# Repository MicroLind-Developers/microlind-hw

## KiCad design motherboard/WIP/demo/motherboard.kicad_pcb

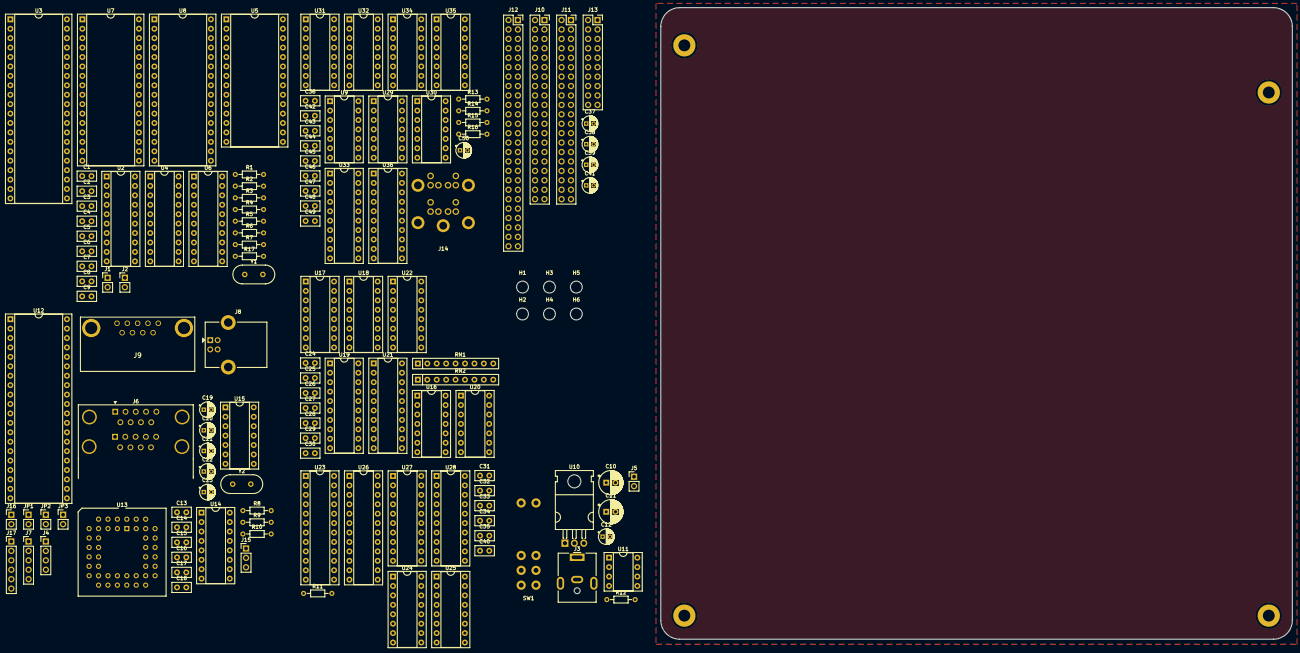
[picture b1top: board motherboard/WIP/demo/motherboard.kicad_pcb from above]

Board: 4 copper layers, 170.2 x 170.2 mm, 134 parts (0 on the bottom side), 218 nets, no tracks yet.

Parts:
C1, C2: 22pF; C_Disc_D5.0mm_W2.5mm_P2.50mm
C3, C4, C5, C6, C7, C8, C9, C13, C14, C17, C18, C24, C25, C26, C27, C28, C29, C30, C31, C32, C33, C34, C35, C36, C40, C42, C43, C44, C45, C46, C47, C48, C49: 100n; C_Disc_D5.0mm_W2.5mm_P2.50mm
C10: 33µF; CP_Radial_D6.3mm_P2.50mm
C11: 100µF; CP_Radial_D6.3mm_P2.50mm
C12: 10µF; CP_Radial_D4.0mm_P2.00mm
C15, C16: 43pF; C_Disc_D5.0mm_W2.5mm_P2.50mm
C19, C20, C21, C22, C23: 1u; CP_Radial_D4.0mm_P2.00mm
C37, C38, C39, C41, C50: 10u; CP_Radial_D4.0mm_P2.00mm
H1, H2, H3, H4, H5, H6: MountingHole; MountingHole_3.2mm_M3_ISO7380
J1: HALT; PinHeader_1x02_P2.54mm_Vertical
J2: Write Enable; PinHeader_1x02_P2.54mm_Vertical
J3: Power; BarrelJack_CUI_PJ-063AH_Horizontal
J4: PowerLed; PinHeader_1x04_P2.54mm_Vertical
J5: Reset; PinHeader_1x02_P2.54mm_Vertical
J6: Joystic Ports; DSUB-9-Double_NorComp
J7: POT Con; PinHeader_1x05_P2.54mm_Vertical
J8: Console; USB_B_Lumberg_2411_02_Horizontal
J9: Serial; 23018431
J10: VideoAddon; PinSocket_2x20_P2.54mm_Vertical
J11: AudioAddon; PinSocket_2x20_P2.54mm_Vertical
J12: ExpansionPort; PinSocket_2x25_P2.54mm_Vertical
J13: Compact Flash Addon; PinSocket_2x10_P2.54mm_Vertical
J14: 2xPS2-Mini-Din
J15: PC Speaker; PinHeader_1x03_P2.54mm_Vertical
J16: LPen; PinHeader_1x02_P2.54mm_Vertical
J17: Clock Exp.; PinHeader_1x06_P2.54mm_Vertical
JP1: Reset EN; PinHeader_1x02_P2.54mm_Vertical
JP2: RTS; PinHeader_1x02_P2.54mm_Vertical
JP3: CTS; PinHeader_1x02_P2.54mm_Vertical
R1, R2, R3, R4, R5, R6, R7, R11, R12, R17: 4k7; R_Axial_DIN0204_L3.6mm_D1.6mm_P7.62mm_Horizontal
R8, R9, R10: 1k; R_Axial_DIN0204_L3.6mm_D1.6mm_P7.62mm_Horizontal
R13, R14, R15, R16: 10k; R_Axial_DIN0204_L3.6mm_D1.6mm_P7.62mm_Horizontal
RN1, RN2: R_Network08; R_Array_SIP9
SW1: Power Switch; CMD-Switch
U1: mITX
U2, U4, U6, U28: 74HC245; DIP-20_W7.62mm_Socket
U3: MC6809; DIP-40_W15.24mm_Socket
U5: 28C64; DIP-28_W15.24mm_Socket
U7, U8: AS6C4008; DIP-32_W15.24mm_Socket
U9, U30: 74HCT14; DIP-14_W7.62mm_Socket
U10: BA05CCOT; TO-220-3_Horizontal_TabDown
U11: MAX708; DIP-8_W7.62mm_Socket
U12: 65c22; DIP-40_W15.24mm_Socket
U13: XR88C92; PLCC-44_THT-Socket
U14: MAX232; DIP-16_W7.62mm_Socket
U15: MCP2221A; DIP-14_W7.62mm_Socket
U16: 74HCT02; DIP-14_W7.62mm_Socket
U17, U18: 74HCT148; DIP-16_W7.62mm_Socket
U19, U21: 74HCT574; DIP-20_W7.62mm_Socket
U20: 74HCT00; DIP-14_W7.62mm_Socket
U22: 74HCT85; DIP-16_W7.62mm_Socket
U23, U26: GAL 22V10; DIP-24_W7.62mm_Socket
U24, U25: 74LS670; DIP-16_W7.62mm_Socket
U27: GAL16V8; DIP-20_W7.62mm_Socket
U29: 74HCT32; DIP-14_W7.62mm_Socket
U31, U32, U34, U35: 74HCT595; DIP-16_W7.62mm_Socket
U33, U36: 74HCT573; DIP-20_W7.62mm_Socket
Y1: 12MHz; Crystal_HC49-U_Vertical
Y2: 3.3864; Crystal_HC49-U_Vertical

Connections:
/A0: J10.32, J11.32, J12.32, J13.6, U2.2 (A0), U5.10 (A0), U7.12 (A0), U8.12 (A0), U12.38 (RS0), U13.2 (A0), U23.10 (I10), U24.14 (Wa), U25.14 (Wa), U26.1 (I1/CLK), U29.4, U30.3
/A1: J10.30, J11.30, J12.30, J13.8, U2.3 (A1), U5.9 (A1), U7.11 (A1), U8.11 (A1), U12.37 (RS1), U13.4 (A1), U23.11 (I11), U24.13 (Wb), U25.13 (Wb), U26.2 (I2)
/A2: J10.28, J11.28, J12.28, J13.10, U2.4 (A2), U5.8 (A2), U7.10 (A2), U8.10 (A2), U12.36 (RS2), U13.6 (A2), U26.3 (I3)
/A3: J10.26, J11.26, J12.26, U2.5 (A3), U5.7 (A3), U7.9 (A3), U8.9 (A3), U12.35 (RS3), U13.7 (A3), U26.4 (I4)
/A4: J10.24, J11.24, J12.24, U2.6 (A4), U5.6 (A4), U7.8 (A4), U8.8 (A4), U26.5 (I5)
/A5: J10.22, J11.22, J12.22, U2.7 (A5), U5.5 (A5), U7.7 (A5), U8.7 (A5), U26.6 (I6)
/A6: J10.20, J11.20, J12.20, U2.8 (A6), U5.4 (A6), U7.6 (A6), U8.6 (A6), U26.7 (I7)
/A7: J10.18, J11.18, J12.18, U2.9 (A7), U5.3 (A7), U7.5 (A7), U8.5 (A7), U26.8 (I8)
/A8: J10.19, J11.19, J12.19, U4.2 (A0), U5.25 (A8), U7.27 (A8), U8.27 (A8), U26.9 (I9)
/A9: J10.21, J11.21, J12.21, U4.3 (A1), U5.24 (A9), U7.26 (A9), U8.26 (A9), U26.10 (I10)
/A10: J10.27, J11.27, J12.27, U4.4 (A2), U5.21 (A10), U7.23 (A10), U8.23 (A10), U23.1 (I1/CLK)
/A11: J10.23, J11.23, J12.23, U4.5 (A3), U5.23 (A11), U7.25 (A11), U8.25 (A11), U23.2 (I2)
/A12: J10.16, J11.16, J12.16, U4.6 (A4), U5.2 (A12), U7.4 (A12), U8.4 (A12), U23.3 (I3)
/A13: J10.17, J11.17, J12.17, U4.7 (A5), U7.28 (A13), U8.28 (A13), U23.4 (I4)
/A14: J12.42, U4.8 (A6), U23.5 (I5)
/A15: J12.44, U4.9 (A7), U23.6 (I6)
/AM14: J10.14, J12.14, U7.3 (A14), U8.3 (A14), U24.10 (Q1), U28.18 (B0)
/AM15: J10.11, J12.11, U7.31 (A15), U8.31 (A15), U24.9 (Q2), U28.17 (B1)
/AM16: J10.12, J12.12, U7.2 (A16), U8.2 (A16), U24.7 (Q3), U28.16 (B2)
/AM17: J10.13, J12.13, U7.30 (A17), U8.30 (A17), U24.6 (Q4), U28.15 (B3)
/AM18: J10.10, J12.10, U7.1 (A18), U8.1 (A18), U25.10 (Q1), U28.14 (B4)
/AM19: J10.9, J12.9, U23.7 (I7), U25.9 (Q2), U28.13 (B5)
/AM20: J10.8, J12.8, U23.8 (I8), U25.7 (Q3), U28.12 (B6)
/AM21: J12.46, U23.9 (I9), U25.6 (Q4), U28.11 (B7)
/Address-Logic/A14/A0: U23.17 (IO7), U24.5 (Ra), U25.5 (Ra)
/Address-Logic/A15/A1: U23.16 (IO8), U24.4 (Rb), U25.4 (Rb)
/Address-Logic/BA: U2.19 (CE), U3.6 (BA), U4.19 (CE), U6.19 (CE), U27.4 (I4)
/Address-Logic/BS: U3.5 (BS), U27.5 (I5)
/Address-Logic/Q: U3.35 (Q), U21.11 (Cp), U27.2 (I2)
/Address-Logic/~CF_EN: J13.7, U26.17 (IO7)
/Address-Logic/~EXP_EN: J12.43, U26.14 (I010)
/Address-Logic/~IO_EN: U23.19 (IO5), U26.11 (I11)
/Address-Logic/~IRQ_EN: U16.3, U16.5, U26.22 (IO2)
/Address-Logic/~MAP_RD: U23.18 (IO6), U24.11 (~Er), U25.11 (~Er)
/Address-Logic/~MEM_EN: U26.23 (IO1), U27.6 (I6)
/Address-Logic/~MEM_RD: U23.13 (I12), U27.16 (IO4), U28.19 (CE)
/Address-Logic/~MEM_WR: U24.12 (~Ew), U25.12 (~Ew), U27.15 (IO5)
/Address-Logic/~PAR_EN: U12.23 (~CS2), U26.19 (IO5)
/Address-Logic/~PS2_EN: U26.18 (IO6), U29.2
/Address-Logic/~RAMH_EN: U8.22 (CE#), U23.21 (I03)
/Address-Logic/~RAML_EN: U7.22 (CE#), U23.22 (IO2)
/Address-Logic/~ROM_EN: U5.20 (~CE), U23.23 (IO1)
/Address-Logic/~SER_EN: U13.39 (~CS), U26.20 (IO4)
/Address-Logic/~SND_EN: J11.3, U26.16 (IO8)
/Address-Logic/~VDC_EN: J10.29, U26.15 (IO9)
/CPU_MEM/MRDY: R6.1, U3.36 (MRDY)
/CPU_MEM/pA0: U2.18 (B0), U3.8 (A0)
/CPU_MEM/pA1: U2.17 (B1), U3.9 (A1)
/CPU_MEM/pA2: U2.16 (B2), U3.10 (A2)
/CPU_MEM/pA3: U2.15 (B3), U3.11 (A3)
/CPU_MEM/pA4: U2.14 (B4), U3.12 (A4)
/CPU_MEM/pA5: U2.13 (B5), U3.13 (A5)
/CPU_MEM/pA6: U2.12 (B6), U3.14 (A6)
/CPU_MEM/pA7: U2.11 (B7), U3.15 (A7)
/CPU_MEM/pA8: U3.16 (A8), U4.18 (B0)
/CPU_MEM/pA9: U3.17 (A9), U4.17 (B1)
/CPU_MEM/pA10: U3.18 (A10), U4.16 (B2)
/CPU_MEM/pA11: U3.19 (A11), U4.15 (B3)
/CPU_MEM/pA12: U3.20 (A12), U4.14 (B4)
/CPU_MEM/pA13: U3.21 (A13), U4.13 (B5)
/CPU_MEM/pA14: U3.22 (A14), U4.12 (B6)
/CPU_MEM/pA15: U3.23 (A15), U4.11 (B7)
/CPU_MEM/pD0: U3.31 (D0), U6.18 (B0)
/CPU_MEM/pD1: U3.30 (D1), U6.17 (B1)
/CPU_MEM/pD2: U3.29 (D2), U6.16 (B2)
/CPU_MEM/pD3: U3.28 (D3), U6.15 (B3)
/CPU_MEM/pD4: U3.27 (D4), U6.14 (B4)
/CPU_MEM/pD5: U3.26 (D5), U6.13 (B5)
/CPU_MEM/pD6: U3.25 (D6), U6.12 (B6)
/CPU_MEM/pD7: U3.24 (D7), U6.11 (B7)
/CPU_MEM/~FIRQ: R4.1, U3.4 (~FIRQ), U22.7 (Oa<b)
/CPU_MEM/~HALT: J1.2, R7.1, U3.40 (~HALT)
/CPU_MEM/~IRQ: R3.1, U3.3 (~IRQ), U12.21 (~IRQ)
/CPU_MEM/~NMI: R2.1, U3.2 (~NMI)
/D0: J10.34, J11.34, J12.34, J13.11, U5.11 (D0), U6.2 (A0), U7.13 (DQ0), U8.13 (DQ0), U12.33 (D0), U13.28 (D0), U21.19 (Q0), U24.15 (D1), U28.2 (A0), U33.19 (Q0), U36.19 (Q0)
/D1: J10.36, J11.36, J12.36, J13.12, U5.12 (D1), U6.3 (A1), U7.14 (DQ1), U8.14 (DQ1), U12.32 (D1), U13.18 (D1), U21.18 (Q1), U24.1 (D2), U28.3 (A1), U33.18 (Q1), U36.18 (Q1)
/D2: J10.38, J11.38, J12.38, J13.13, U5.13 (D2), U6.4 (A2), U7.15 (DQ2), U8.15 (DQ2), U12.31 (D2), U13.27 (D2), U21.17 (Q2), U24.2 (D3), U28.4 (A2), U33.17 (Q2), U36.17 (Q2)
/D3: J10.39, J11.39, J12.39, J13.14, U5.15 (D3), U6.5 (A3), U7.17 (DQ3), U8.17 (DQ3), U12.30 (D3), U13.19 (D3), U21.16 (Q3), U24.3 (D4), U28.5 (A3), U33.16 (Q3), U36.16 (Q3)
/D4: J10.37, J11.37, J12.37, J13.15, U5.16 (D4), U6.6 (A4), U7.18 (DQ4), U8.18 (DQ4), U12.29 (D4), U13.26 (D4), U19.2 (D0), U21.15 (Q4), U25.15 (D1), U28.6 (A4), U33.15 (Q4), U36.15 (Q4)
/D5: J10.35, J11.35, J12.35, J13.16, U5.17 (D5), U6.7 (A5), U7.19 (DQ5), U8.19 (DQ5), U12.28 (D5), U13.20 (D5), U19.3 (D1), U21.14 (Q5), U25.1 (D2), U28.7 (A5), U33.14 (Q5), U36.14 (Q5)
/D6: J10.33, J11.33, J12.33, J13.17, U5.18 (D6), U6.8 (A6), U7.20 (DQ6), U8.20 (DQ6), U12.27 (D6), U13.25 (D6), U19.4 (D2), U21.13 (Q6), U25.2 (D3), U28.8 (A6), U33.13 (Q6), U36.13 (Q6)
/D7: J10.31, J11.31, J12.31, J13.18, U5.19 (D7), U6.9 (A7), U7.21 (DQ7), U8.21 (DQ7), U12.26 (D7), U13.21 (D7), U19.5 (D3), U21.12 (Q7), U25.3 (D4), U28.9 (A7), U33.12 (Q7), U36.12 (Q7)
/Expansion Ports/BAVAIL: J10.7, J12.7, U27.17 (I03)
/Expansion Ports/E: J10.5, J11.5, J12.5, J13.3, U3.34 (E), U12.25 (ϕ2), U27.1 (I1/CLK), U31.12 (RCLK), U32.12 (RCLK), U34.12 (RCLK), U35.12 (RCLK)
/Expansion Ports/R/~W: J10.6, J11.6, J12.6, U3.32 (R/~W), U6.1 (A->B), U12.22 (R/~W), U27.3 (I3)
/Expansion Ports/~BREQ: J10.3, J12.3, R5.1, U3.33 (~DMA/BREQ), U27.11 (I10/~OE)
/Expansion Ports/~MAP_EN: J12.41, R11.1, U23.14 (I010)
/Expansion Ports/~RAMX_EN: J12.29, U23.20 (IO4)
/Expansion Ports/~RD: J10.25, J11.25, J12.25, J13.5, U5.22 (~OE), U7.24 (OE#), U8.24 (OE#), U13.10 (~RD), U16.2, U27.18 (IO2), U29.1
/Expansion Ports/~RST: J10.2, J11.2, J12.2, J13.2, JP1.2 (B), R1.1, U3.37 (~RESET), U11.7 (~RST), U12.34 (~RES), U31.10 (~SRCLR), U32.10 (~SRCLR), U34.10 (~SRCLR), U35.10 (~SRCLR)
/Expansion Ports/~WR: J2.2, J10.15, J11.15, J12.15, J13.4, U7.29 (WE#), U8.29 (WE#), U13.9 (~WR), U16.6, U26.13 (I12), U27.19 (IO1)
/PS2/M_CLK: U9.2, U31.11 (SRCLK), U32.11 (SRCLK)
/PS2/M_DATA: U9.4, U31.14 (SER)
/PS2/PS2_KB_CLK: J14.11 (Kbd_Clock), R15.2, U30.1
/PS2/PS2_KB_DATA: J14.7 (Kbd_Data), R16.2, U30.5
/PS2/PS2_M_CLK: J14.5 (Mouse_Clock), R13.2, U9.13
/PS2/PS2_M_DATA: J14.1 (Mouse_Data), R14.2, U9.11
/Power-Management/RST: U11.8 (RST), U13.38 (RST)
/Serial-Parallel/D+: J8.3 (D+), U15.13 (D+)
/Serial-Parallel/D-: J8.2 (D-), U15.12 (D-)
/~IRQ_0: RN2.6 (R5), U13.24 (~INT), U18.4 (I7)
/~IRQ_1: RN2.7 (R6), U18.3 (I6)
/~IRQ_2: J10.4, RN2.8 (R7), U18.2 (I5)
/~IRQ_3: RN2.9 (R8), U18.1 (I4)
/~IRQ_4: RN2.5 (R4), U18.13 (I3)
/~IRQ_5: RN2.4 (R3), U18.12 (I2)
/~IRQ_6: RN2.3 (R2), U18.11 (I1)
/~IRQ_7: J11.4, RN2.2 (R1), U18.10 (IO)
/~IRQ_8: J12.4, RN1.6 (R5), U17.4 (I7)
/~IRQ_9: RN1.7 (R6), U17.3 (I6)
/~IRQ_10: RN1.8 (R7), U17.2 (I5)
/~IRQ_11: RN1.9 (R8), U17.1 (I4)
/~IRQ_12: RN1.5 (R4), U17.13 (I3)
/~IRQ_13: RN1.4 (R3), U17.12 (I2)
/~IRQ_14: RN1.3 (R2), U17.11 (I1)
GND: C1.2, C2.2, C3.2, C4.2, C5.2, C6.2, C7.2, C8.2, C9.2, C10.2, C11.2, C12.2, C13.2, C14.2, C15.2, C16.2, C17.2, C18.2, C22.2, C23.2, C24.2, C25.2, C26.2, C27.2, C28.2, C29.2, C30.2, C31.2, C32.2, C33.2, C34.2, C35.2, C36.2, C37.2, C38.2, C39.2, C40.2, C41.2, C42.2, C43.2, C44.2, C45.2, C46.2, C47.2, C48.2, C49.2, C50.2, J1.1, J3.2, J3.MP (MountPin), J4.1 (K), J5.1, J6.8, J6.18, J7.3, J8.4 (GND), J8.5 (Shield), J9.5, J10.40, J11.40, J12.40, J12.48, J12.50, J13.20, J14.3 (Mouse_GND), J14.9 (Kbd_GND), J14.G (GND), J15.1, J16.1, J17.1, R11.2, SW1.G (GND), U2.1 (A->B), U2.10 (GND), U3.1 (VSS), U4.1 (A->B), U4.10 (GND), U5.14 (GND), U6.10 (GND), U7.16 (VSS), U8.16 (VSS), U9.7 (GND), U10.2 (GND), U11.3 (GND), U12.1 (VSS), U13.22 (GND), U14.15 (GND), U15.14 (VSS), U16.7 (GND), U17.8 (GND), U18.5 (EI), U18.8 (GND), U19.1 (OE), U19.10 (GND), U20.7 (GND), U21.10 (GND), U22.2 (Ia<b), U22.3 (Ia=b), U22.4 (Ia>b), U22.8 (GND), U23.12 (GND), U24.8 (GND), U25.8 (GND), U26.12 (GND), U27.10 (GND), U28.1 (A->B), U28.10 (GND), U29.7 (GND), U29.12, U29.13, U30.7 (GND), U31.8 (GND), U31.13 (~OE), U32.8 (GND), U32.13 (~OE), U33.10 (GND), U34.8 (GND), U34.13 (~OE), U35.8 (GND), U35.13 (~OE), U36.10 (GND)
unnamed: J2.1, R17.1, U5.27 (~WE)
unnamed: J4.4 (BA), R10.1
unnamed: J4.3 (GA), R9.1
unnamed: J4.2 (RA), R8.1
unnamed: J6.5, J7.1
unnamed: J6.9, J7.2
unnamed: J6.15, J7.4
unnamed: J6.19, J7.5
unnamed: J15.2, U12.17 (PB7)
unnamed: J6.6, J16.2, U12.6 (PA4)
unnamed: J17.2, U12.18 (CB1)
unnamed: J17.3, U12.19 (CB2)
unnamed: J17.4, U12.40 (CA1)
unnamed: J17.5, U12.9 (PA7)
unnamed: JP1.1 (A), U15.4 (~RST)
unnamed: JP2.1 (A), U13.32 (OP0)
unnamed: JP2.2 (B), U15.2 (GP0)
unnamed: JP3.1 (A), U13.8 (IP0)
unnamed: JP3.2 (B), U15.3 (GP1)
unnamed: C10.1, SW1.3 (1-2), SW1.6 (2-2), U10.1 (Vin)
unnamed: J3.1, SW1.1 (1-C), SW1.4 (2-C)
unnamed: C2.1, U3.38 (EXTAL), Y1.1
unnamed: C1.1, U3.39 (XTAL), Y1.2
unnamed: U9.1, U9.12
unnamed: U9.3, U9.10
unnamed: J5.2, R12.2, U11.1 (~MR)
unnamed: J6.1, U12.2 (PA0)
unnamed: J6.2, U12.3 (PA1)
unnamed: J6.3, U12.4 (PA2)
unnamed: J6.4, U12.5 (PA3)
unnamed: J6.11, U12.10 (PB0)
unnamed: J6.12, U12.11 (PB1)
unnamed: J6.13, U12.12 (PB2)
unnamed: J6.14, U12.13 (PB3)
unnamed: J6.16, U12.14 (PB4)
unnamed: R8.2, U13.30 (OP4)
unnamed: R10.2, U13.16 (OP5)
unnamed: R9.2, U13.29 (OP6)
unnamed: U13.35 (RxA), U15.6 (UTx)
unnamed: U13.11 (RxB), U14.12 (R1OUT)
unnamed: U13.33 (TxA), U15.5 (URx)
unnamed: U13.13 (TxB), U14.11 (T1IN)
unnamed: C15.1, U13.36 (X1/CLK), Y2.2
unnamed: C16.1, U13.37 (X2), Y2.1
unnamed: C19.1, U14.1 (C1+)
unnamed: C19.2, U14.3 (C1-)
unnamed: C20.1, U14.4 (C2+)
unnamed: C20.2, U14.5 (C2-)
unnamed: J9.2, U14.13 (R1IN)
unnamed: J9.3, U14.14 (T1OUT)
unnamed: C21.1, U14.2 (VS+)
unnamed: C21.2, U14.6 (VS-)
unnamed: C23.1, U15.11 (VUSB)
unnamed: U16.1, U16.8, U16.9
unnamed: U17.5 (EI), U18.15 (EO)
unnamed: U17.9 (S0), U20.12
unnamed: U17.7 (S1), U20.9
unnamed: U17.6 (S2), U20.4
unnamed: U18.14 (GS), U20.1, U20.2
unnamed: U18.9 (S0), U20.13
unnamed: U18.7 (S1), U20.10
unnamed: U18.6 (S2), U20.5
unnamed: U16.4, U19.11 (Cp)
unnamed: U19.19 (Q0), U21.6 (D4), U22.10 (A0)
unnamed: U19.18 (Q1), U21.7 (D5), U22.12 (A1)
unnamed: U19.17 (Q2), U21.8 (D6), U22.13 (A2)
unnamed: U19.16 (Q3), U21.9 (D7), U22.15 (A3)
unnamed: U20.6, U21.2 (D0), U22.9 (B0)
unnamed: U20.8, U21.3 (D1), U22.11 (B1)
unnamed: U20.11, U21.4 (D2), U22.14 (B2)
unnamed: U20.3, U21.5 (D3), U22.1 (B3)
unnamed: U16.10, U21.1 (OE)
unnamed: U29.3, U29.5, U29.9
unnamed: U29.10, U30.4
unnamed: U30.6, U30.11
unnamed: U30.2, U30.13
unnamed: U31.2 (QC), U33.9 (D7)
unnamed: U31.3 (QD), U33.8 (D6)
unnamed: U31.4 (QE), U33.7 (D5)
unnamed: U31.5 (QF), U33.6 (D4)
unnamed: U31.6 (QG), U33.5 (D3)
unnamed: U31.9 (QH'), U32.14 (SER)
unnamed: U31.7 (QH), U33.4 (D2)
unnamed: U32.15 (QA), U33.3 (D1)
unnamed: U32.1 (QB), U33.2 (D0)
unnamed: U9.9, U32.2 (QC), U33.11 (Load)
unnamed: U29.8, U33.1 (OE)
unnamed: U34.2 (QC), U36.9 (D7)
unnamed: U34.3 (QD), U36.8 (D6)
unnamed: U34.4 (QE), U36.7 (D5)
unnamed: U34.5 (QF), U36.6 (D4)
unnamed: U34.6 (QG), U36.5 (D3)
unnamed: U34.9 (QH'), U35.14 (SER)
unnamed: U34.7 (QH), U36.4 (D2)
unnamed: U30.10, U34.14 (SER)
unnamed: U30.12, U34.11 (SRCLK), U35.11 (SRCLK)
unnamed: U35.15 (QA), U36.3 (D1)
unnamed: U35.1 (QB), U36.2 (D0)
unnamed: U30.9, U35.2 (QC), U36.11 (Load)
unnamed: U29.6, U36.1 (OE)
VCC: C3.1, C4.1, C5.1, C6.1, C7.1, C8.1, C9.1, C11.1, C12.1, C13.1, C14.1, C17.1, C18.1, C22.1, C24.1, C25.1, C26.1, C27.1, C28.1, C29.1, C30.1, C31.1, C32.1, C33.1, C34.1, C35.1, C36.1, C37.1, C38.1, C39.1, C40.1, C41.1, C42.1, C43.1, C44.1, C45.1, C46.1, C47.1, C48.1, C49.1, C50.1, J6.7, J6.17, J10.1, J11.1, J12.1, J12.47, J12.49, J13.1, J14.4 (Mouse_PWR), J14.10 (Kbd_PWR), J15.3, J17.6, R1.2, R2.2, R3.2, R4.2, R5.2, R6.2, R7.2, R12.1, R13.1, R14.1, R15.1, R16.1, R17.2, RN1.1 (common), RN2.1 (common), U2.20 (VCC), U3.7 (VCC), U4.20 (VCC), U5.28 (VCC), U6.20 (VCC), U7.32 (VCC), U8.32 (VCC), U9.5, U9.14 (VCC), U10.3 (Vout), U11.2 (VCC), U12.20 (VCC), U12.24 (CS1), U13.44 (VCC), U14.16 (VCC), U15.1 (VDD), U16.11, U16.12, U16.14 (VCC), U17.16 (VCC), U18.16 (VCC), U19.20 (VCC), U20.14 (VCC), U21.20 (VCC), U22.16 (VCC), U23.24 (VCC), U24.16 (VCC), U25.16 (VCC), U26.24 (VCC), U27.20 (VCC), U28.20 (VCC), U29.14 (VCC), U30.14 (VCC), U31.16 (VCC), U32.16 (VCC), U33.20 (VCC), U34.16 (VCC), U35.16 (VCC), U36.20 (VCC)
~RD': U27.9 (I9), U27.12 (IO8)

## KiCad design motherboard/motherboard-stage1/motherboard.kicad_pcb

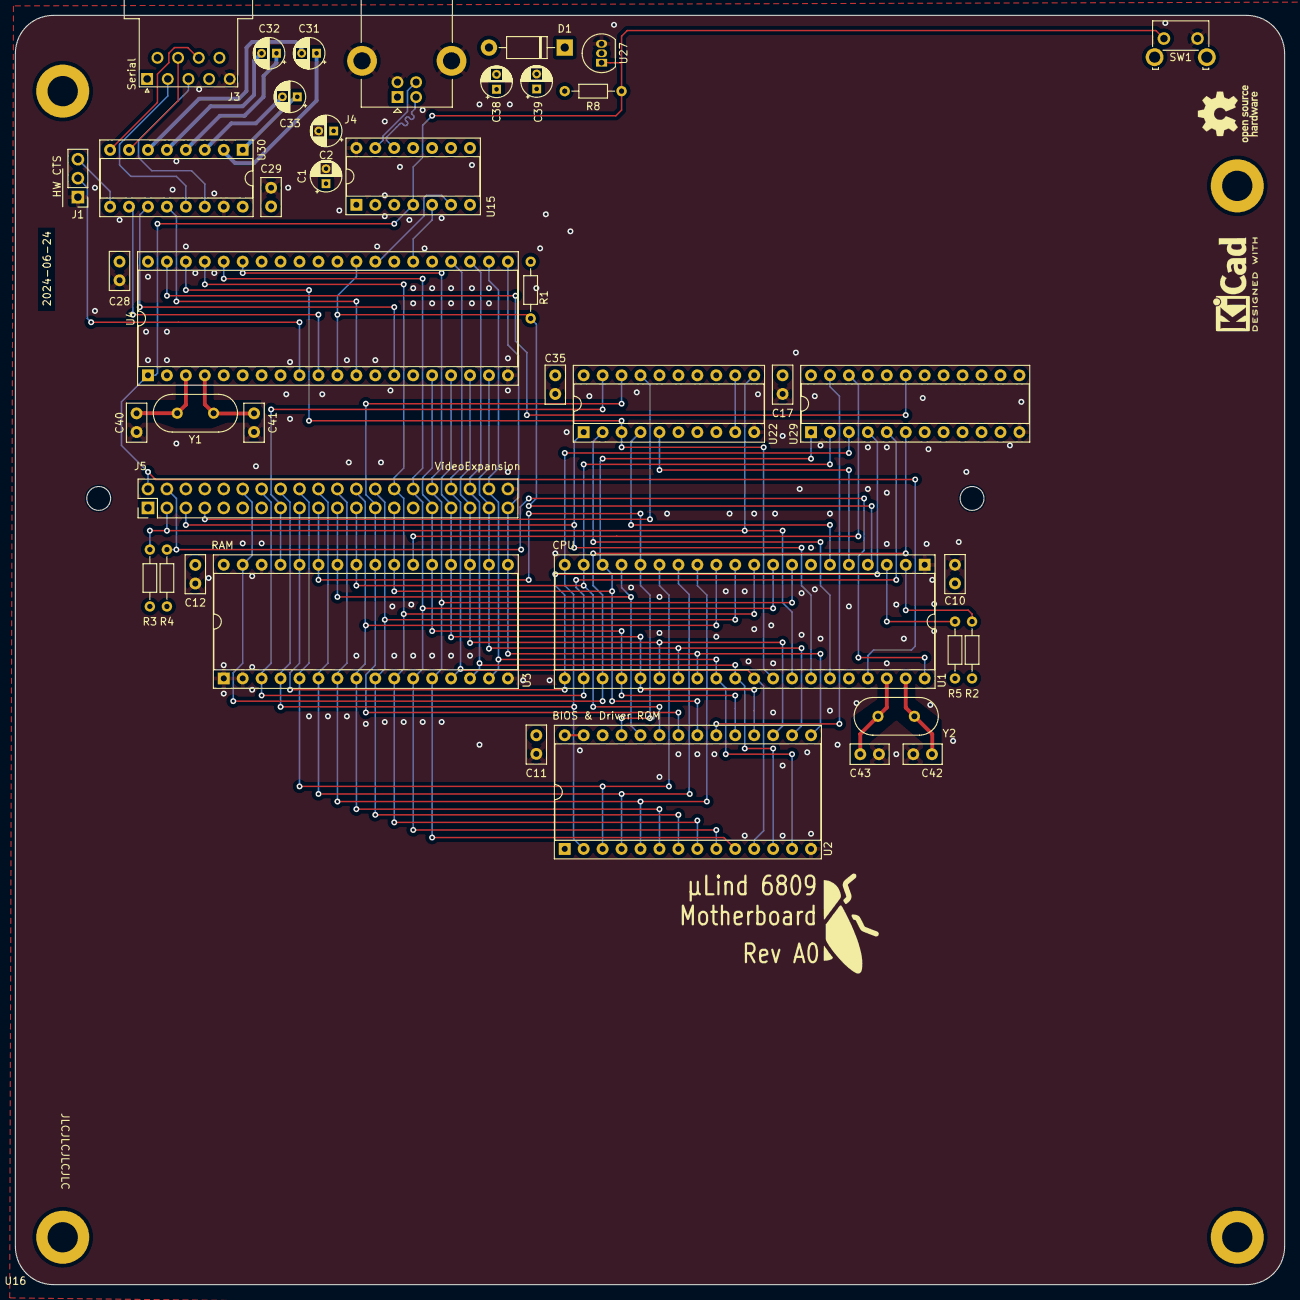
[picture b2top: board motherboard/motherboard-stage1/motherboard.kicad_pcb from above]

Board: 4 copper layers, 170.2 x 170.2 mm, 44 parts (0 on the bottom side), 69 nets.

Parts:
C1, C2, C31, C32, C33: 1u; CP_Radial_D4.0mm_P2.00mm
C10, C11, C12, C17, C28, C29, C35: C; C_Disc_D5.0mm_W2.5mm_P2.50mm
C38: 100µF; CP_Radial_D4.0mm_P2.00mm
C39: 10µF; CP_Radial_D4.0mm_P2.00mm
C40, C41: 43pF; C_Disc_D5.0mm_W2.5mm_P2.50mm
C42, C43: 24pF; C_Disc_D5.0mm_W2.5mm_P2.50mm
D1: 1N4007; D_DO-41_SOD81_P10.16mm_Horizontal
H6, H8: MountingHole; MountingHole_3.2mm_M3_ISO7380
J1: HW CTS; PinHeader_1x03_P2.54mm_Vertical
J3: Serial; DSUB-9_Female_Horizontal_P2.77x2.84mm_EdgePinOffset9.40mm
J4: Console; USB_B_Lumberg_2411_02_Horizontal
J5: VideoExpansion; PinHeader_2x20_P2.54mm_Vertical
R1, R2, R3, R4, R5, R8: 4k7; R_Axial_DIN0204_L3.6mm_D1.6mm_P7.62mm_Horizontal
SW1: Reset; SW_SPST_Omron_B3F-315x_Angled
U1: MC6809; DIP-40_W15.24mm_Socket
U2: 28C64; DIP-28_W15.24mm_Socket
U3: AS6C4008; DIP-32_W15.24mm_Socket
U4: DIP-40_W15.24mm_Socket
U15: MCP2221A; DIP-14_W7.62mm_Socket
U16: mITX
U22: GAL16V8; DIP-20_W7.62mm_Socket
U27: DS1813; TO-92_Inline
U29: GAL 22V10; DIP-24_W7.62mm_Socket
U30: MAX232; DIP-16_W7.62mm_Socket
Y1, Y2: Crystal; Crystal_HC49-U_Vertical

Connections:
/A0: J5.32, U1.8 (A0), U2.10 (A0), U3.12 (A0), U4.35 (RS0)
/A1: J5.30, U1.9 (A1), U2.9 (A1), U3.11 (A1), U4.36 (RS1)
/A2: J5.28, U1.10 (A2), U2.8 (A2), U3.10 (A2), U4.37 (RS2)
/A3: J5.26, U1.11 (A3), U2.7 (A3), U3.9 (A3)
/A4: J5.24, U1.12 (A4), U2.6 (A4), U3.8 (A4)
/A5: J5.22, U1.13 (A5), U2.5 (A5), U3.7 (A5)
/A6: J5.20, U1.14 (A6), U2.4 (A6), U3.6 (A6)
/A7: J5.18, U1.15 (A7), U2.3 (A7), U3.5 (A7)
/A8: J5.19, U1.16 (A8), U2.25 (A8), U3.27 (A8)
/A9: J5.21, U1.17 (A9), U2.24 (A9), U3.26 (A9)
/A10: J5.27, U1.18 (A10), U2.21 (A10), U3.23 (A10), U29.1 (I1/CLK)
/A11: J5.23, U1.19 (A11), U2.23 (A11), U3.25 (A11), U29.2 (I2)
/A12: J5.16, U1.20 (A12), U2.2 (A12), U3.4 (A12), U29.3 (I3)
/A13: J5.17, U1.21 (A13), U3.28 (A13), U29.4 (I4)
/A14: J5.14, U1.22 (A14), U3.3 (A14), U29.5 (I5)
/A15: J5.12, U1.23 (A15), U3.31 (A15), U29.6 (I6)
/Address-Logic/BA: U1.6 (BA), U22.4 (I4)
/Address-Logic/BS: U1.5 (BS), U22.5 (I5)
/Address-Logic/Q: U1.35 (Q), U22.2 (I2)
/Address-Logic/R/~W: U1.32 (R/~W), U4.38 (R~W), U22.3 (I3)
/Address-Logic/~RAM_EN: U3.22 (CE#), U29.22 (IO2)
/Address-Logic/~ROM_EN: U2.20 (~CE), U29.23 (IO1)
/Address-Logic/~SER_EN: U4.39 (~CS), U29.19 (IO5)
/CPU_MEM/~FIRQ: R1.1, U1.4 (~FIRQ), U4.11 (~IRQ2), U4.29 (~IRQ1)
/CPU_MEM/~HALT: J5.4, R4.1, U1.40 (~HALT)
/CPU_MEM/~IRQ: R5.1, U1.3 (~IRQ)
/CPU_MEM/~NMI: R2.1, U1.2 (~NMI)
/D0: J5.34, U1.31 (D0), U2.11 (D0), U3.13 (DQ0), U4.24 (D0)
/D1: J5.36, U1.30 (D1), U2.12 (D1), U3.14 (DQ1), U4.23 (D1)
/D2: J5.38, U1.29 (D2), U2.13 (D2), U3.15 (DQ2), U4.22 (D2)
/D3: J5.39, U1.28 (D3), U2.15 (D3), U3.17 (DQ3), U4.21 (D3)
/D4: J5.37, U1.27 (D4), U2.16 (D4), U3.18 (DQ4), U4.19 (D4)
/D5: J5.35, U1.26 (D5), U2.17 (D5), U3.19 (DQ5), U4.18 (D5)
/D6: J5.33, U1.25 (D6), U2.18 (D6), U3.20 (DQ6), U4.17 (D6)
/D7: J5.31, U1.24 (D7), U2.19 (D7), U3.21 (DQ7), U4.16 (D7)
/Expansion Ports/BAVAIL: J5.7, U22.17 (I03)
/Expansion Ports/E: J5.5, U1.34 (E), U22.1 (I1/CLK)
/Expansion Ports/~BREQ: J5.3, R3.1, U1.33 (~DMA/BREQ), U22.11 (I10/~OE)
/Expansion Ports/~RD: J5.25, U2.22 (~OE), U3.24 (OE#), U22.18 (IO2)
/Expansion Ports/~RST: J5.2, R8.2, SW1.1, U1.37 (~RESET), U4.1 (~RST), U15.4 (~RST), U27.1 (~RST)
/Expansion Ports/~WR: J5.15, U3.29 (WE#), U22.19 (IO1)
/Serial-Parallel/D+: J4.3 (D+), U15.13 (D+)
/Serial-Parallel/D-: J4.2 (D-), U15.12 (D-)
GND: C1.2, C2.2, C10.2, C11.2, C12.2, C17.2, C28.2, C29.2, C35.2, C40.2, C41.2, C42.2, C43.2, J1.1, J3.5, J4.4 (GND), J4.5 (Shield), J5.40, SW1.2, U1.1 (VSS), U2.14 (GND), U3.1 (A18), U3.2 (A16), U3.16 (VSS), U3.30 (A17), U4.20 (Vss), U15.14 (VSS), U22.10 (GND), U27.3 (GND), U29.12 (GND), U30.15 (GND)
unnamed: J1.2, U4.9 (~CTS2)
unnamed: J1.3, U30.9 (R2OUT)
unnamed: C43.1, U1.38 (EXTAL), Y2.1
unnamed: C42.1, U1.39 (XTAL), Y2.2
unnamed: C40.1, U4.3 (X1), Y1.2
unnamed: C41.1, U4.4 (X2), Y1.1
unnamed: U4.26 (TxD1), U15.5 (URx)
unnamed: U4.28 (RxD1), U15.6 (UTx)
unnamed: C2.1, U15.11 (VUSB)
unnamed: C33.1, U30.1 (C1+)
unnamed: C33.2, U30.3 (C1-)
unnamed: C32.1, U30.4 (C2+)
unnamed: C32.2, U30.5 (C2-)
unnamed: J3.2, U30.13 (R1IN)
unnamed: U4.12 (RxD2), U30.12 (R1OUT)
unnamed: J3.8, U30.8 (R2IN)
unnamed: U4.14 (TxD2), U30.11 (T1IN)
unnamed: J3.3, U30.14 (T1OUT)
unnamed: U4.10 (~RTS2), U30.10 (T2IN)
unnamed: J3.7, U30.7 (T2OUT)
unnamed: C31.1, U30.2 (VS+)
unnamed: C31.2, U30.6 (VS-)
VBUS: C1.1, C38.1, C39.1, D1.2 (A), J4.1 (VBUS), U15.1 (VDD)
VCC: C10.1, C11.1, C12.1, C17.1, C28.1, C29.1, C35.1, C38.2, C39.2, D1.1 (K), J5.1, R1.2, R2.2, R3.2, R4.2, R5.2, R8.1, U1.7 (VCC), U2.27 (~WE), U2.28 (VCC), U3.32 (VCC), U4.40 (VCC), U22.20 (VCC), U27.2 (VCC), U29.24 (VCC), U30.16 (VCC)
~RD': U22.9 (I9), U22.12 (IO8)

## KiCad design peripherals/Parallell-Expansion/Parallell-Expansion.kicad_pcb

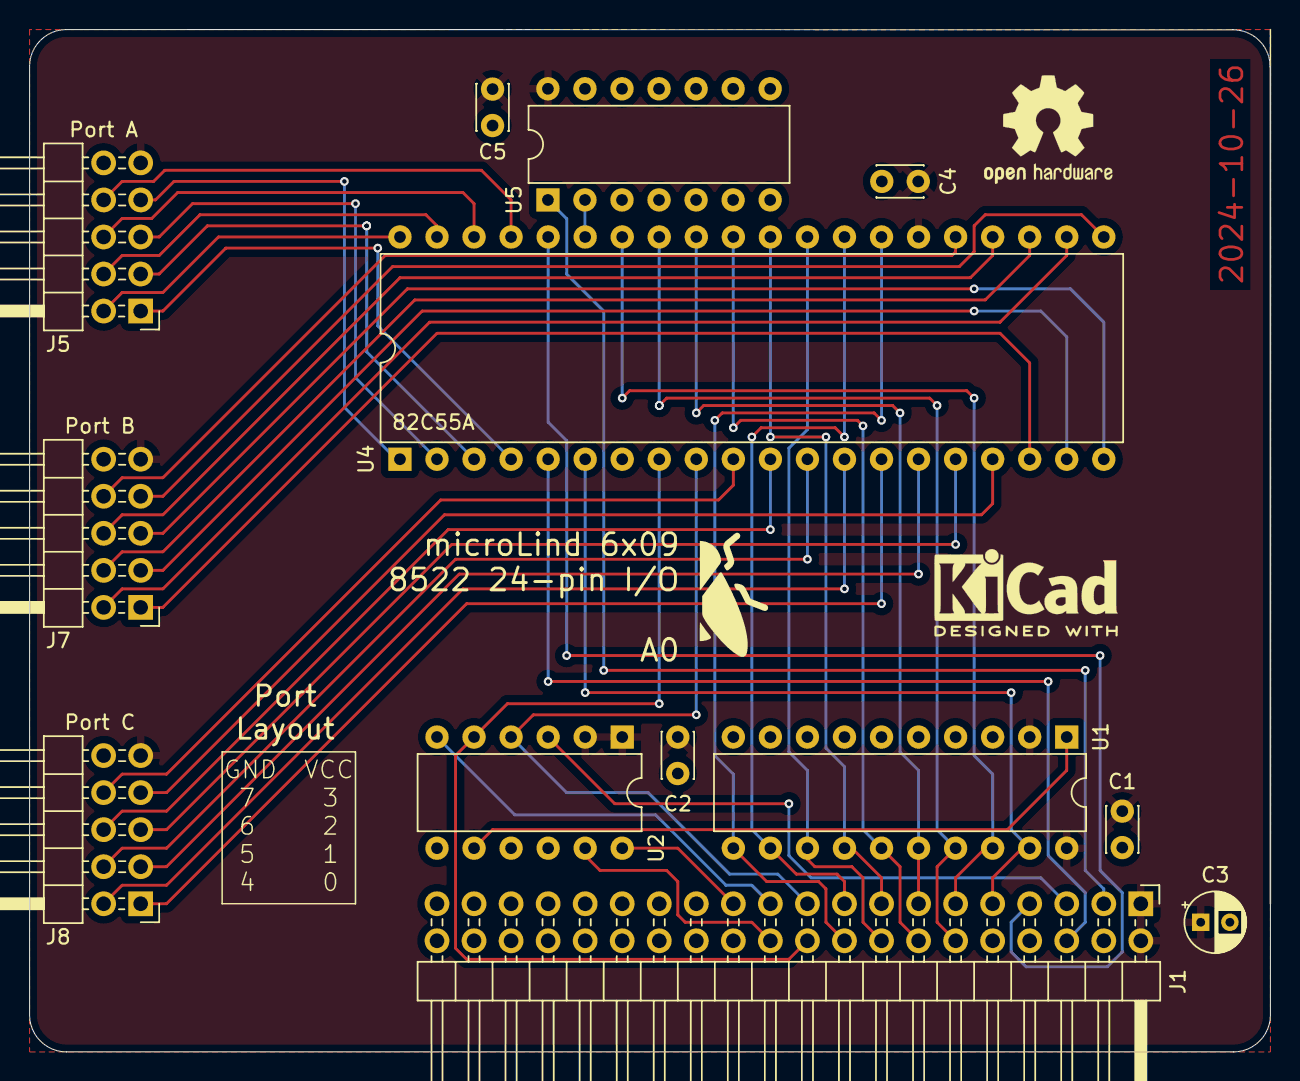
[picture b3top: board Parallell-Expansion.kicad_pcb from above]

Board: 2 copper layers, 85.1 x 70.1 mm, 13 parts (0 on the bottom side), 46 nets.

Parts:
C1, C2, C4, C5: 100n; C_Disc_D3.0mm_W2.0mm_P2.50mm
C3: 10µ; CP_Radial_D4.0mm_P2.00mm
J1: Conn_02x20_Odd_Even; PinHeader_2x20_P2.54mm_Horizontal
J5: Port A; PinHeader_2x05_P2.54mm_Horizontal
J7: Port B; PinHeader_2x05_P2.54mm_Horizontal
J8: Port C; PinHeader_2x05_P2.54mm_Horizontal
U1: 74LS541; DIP-20_W7.62mm
U2: 74LS30; DIP-12_W7.62mm
U4: 82C55A; DIP-40_W15.24mm
U5: 74LS04; DIP-14_W7.62mm

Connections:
A0: J1.19, U2.4, U4.9 (A0)
A1: J1.20, U2.5, U4.8 (A1)
A2: J1.21, U2.6
A3: J1.22, U2.11
A4: J1.23, U2.12
D0: J1.11, U1.18 (Y0), U4.34 (D0)
D1: J1.12, U1.17 (Y1), U4.33 (D1)
D2: J1.13, U1.16 (Y2), U4.32 (D2)
D3: J1.14, U1.15 (Y3), U4.31 (D3)
D4: J1.15, U1.14 (Y4), U4.30 (D4)
D5: J1.16, U1.13 (Y5), U4.29 (D5)
D6: J1.17, U1.12 (Y6), U4.28 (D6)
D7: J1.18, U1.11 (Y7), U4.27 (D7)
GND: C1.2, C2.2, C3.2, C4.2, C5.2, J1.39, J1.40, J5.10, J7.10, J8.10, U1.3 (A1), U1.4 (A2), U1.5 (A3), U1.6 (A4), U1.7 (A5), U1.8 (A6), U1.9 (A7), U1.10 (GND), U4.7 (GND), U5.3, U5.5, U5.7 (GND), U5.9, U5.11, U5.13
unnamed: J5.1, U4.4 (PA0)
unnamed: J5.3, U4.3 (PA1)
unnamed: J5.5, U4.2 (PA2)
unnamed: J5.7, U4.1 (PA3)
unnamed: J7.1, U4.18 (PB0)
unnamed: J7.3, U4.19 (PB1)
unnamed: J7.5, U4.20 (PB2)
unnamed: J7.7, U4.21 (PB3)
unnamed: J8.1, U4.14 (PC0)
unnamed: J8.3, U4.15 (PC1)
unnamed: J8.5, U4.16 (PC2)
unnamed: J8.7, U4.17 (PC3)
unnamed: U1.1 (G1), U2.8
unnamed: U4.35 (RESET), U5.2
PA4: J5.2, U4.40 (PA4)
PA5: J5.4, U4.39 (PA5)
PA6: J5.6, U4.38 (PA6)
PA7: J5.8, U4.37 (PA7)
PB4: J7.2, U4.22 (PB4)
PB5: J7.4, U4.23 (PB5)
PB6: J7.6, U4.24 (PB6)
PB7: J7.8, U4.25 (PB7)
PC4: J8.2, U4.13 (PC4)
PC5: J8.4, U4.12 (PC5)
PC6: J8.6, U4.11 (PC6)
PC7: J8.8, U4.10 (PC7)
R/_W: J1.5, U2.3
VCC: C1.1, C2.1, C3.1, C4.1, C5.1, J1.1, J1.2, J5.9, J7.9, J8.9, U1.2 (A0), U1.20 (VCC), U2.1, U2.2, U4.26 (VCC), U5.14 (VCC)
_EN: J1.9, U1.19 (G2), U4.6 (~CS)
_RD: J1.6, U4.5 (~RD)
_RST: J1.3, U5.1
_WR: J1.7, U4.36 (~WR)

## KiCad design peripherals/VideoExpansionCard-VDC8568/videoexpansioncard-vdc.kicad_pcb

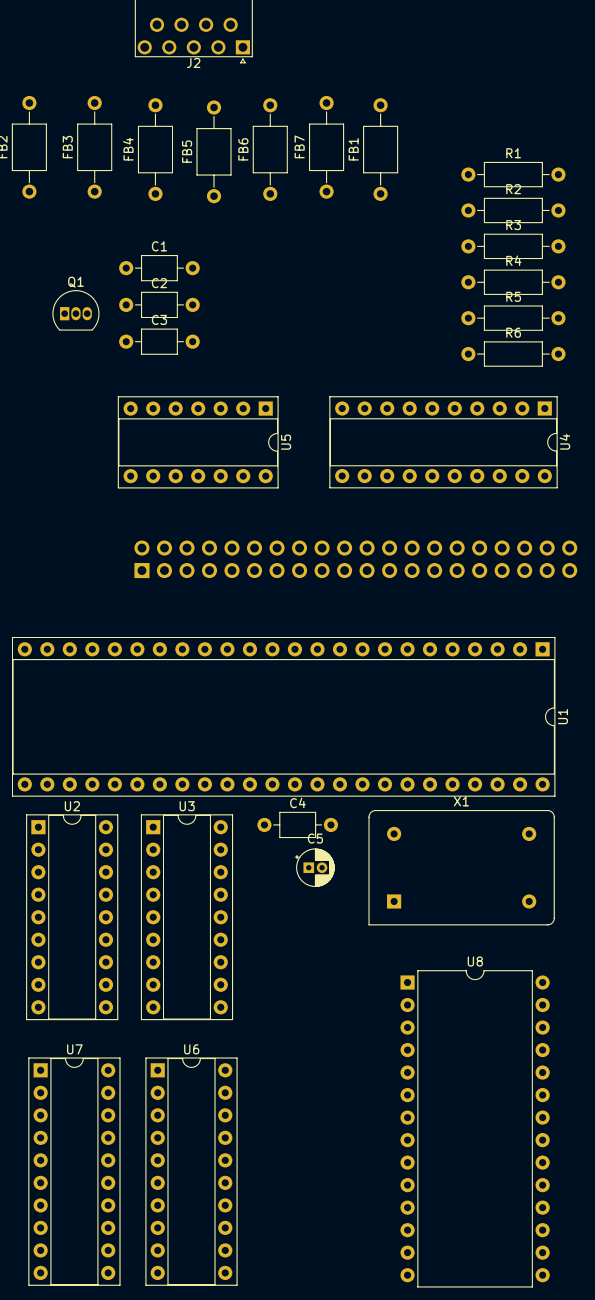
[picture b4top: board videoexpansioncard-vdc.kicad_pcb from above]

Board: 2 copper layers, 30 parts (1 on the bottom side), 69 nets, no tracks yet.

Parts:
C1, C4: 100nF; C_Axial_L3.8mm_D2.6mm_P7.50mm_Horizontal
C2, C3: 220nF; C_Axial_L3.8mm_D2.6mm_P7.50mm_Horizontal
C5: 10µF; CP_Radial_D4.0mm_P1.50mm
FB1, FB2, FB3, FB4, FB5, FB6, FB7: FerriteBead_Small; L_Axial_L5.0mm_D3.6mm_P10.00mm_Horizontal_Murata_BL01RN1A2A2
J1: VEP; PinSocket_2x20_P2.54mm_Vertical
J2: DE9_Plug; DSUB-9_Male_Horizontal_P2.77x2.54mm_EdgePinOffset9.40mm
Q1: 2SC1815; TO-92_Inline
R1, R2: 120; R_Axial_DIN0207_L6.3mm_D2.5mm_P10.16mm_Horizontal
R3: 100; R_Axial_DIN0207_L6.3mm_D2.5mm_P10.16mm_Horizontal
R4: 330; R_Axial_DIN0207_L6.3mm_D2.5mm_P10.16mm_Horizontal
R5: 47; R_Axial_DIN0207_L6.3mm_D2.5mm_P10.16mm_Horizontal
R6: 82; R_Axial_DIN0207_L6.3mm_D2.5mm_P10.16mm_Horizontal
U1: 8568; DIP-48_W15.24mm_Socket
U2, U3: DIP-18_W7.62mm_Socket
U4: 74HCT244; DIP-20_W7.62mm_Socket
U5: 74LS07; DIP-14_W7.62mm_Socket
U6: 74HCT273; DIP-20_W7.62mm_Socket
U7: GAL16V8; DIP-20_W7.62mm_Socket
U8: 27C64; DIP-28_W15.24mm
X1: ACO-16MHz; Oscillator_DIP-14

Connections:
/DRAM.DA0: U1.26 (DA0), U2.14 (A0), U3.14 (A0)
/DRAM.DA1: U1.27 (DA1), U2.13 (A1), U3.13 (A1)
/DRAM.DA2: U1.28 (DA2), U2.12 (A2), U3.12 (A2)
/DRAM.DA3: U1.29 (DA3), U2.11 (A3), U3.11 (A3)
/DRAM.DA4: U1.30 (DA4), U2.8 (A4), U3.8 (A4)
/DRAM.DA5: U1.31 (DA5), U2.7 (A5), U3.7 (A5)
/DRAM.DA6: U1.32 (DA6), U2.6 (A6), U3.6 (A6)
/DRAM.DA7: U1.33 (DA7), U2.10 (A7), U3.10 (A7)
/DRAM.DD0: U1.34 (DD0), U2.2 (D0)
/DRAM.DD1: U1.35 (DD1), U2.3 (D1)
/DRAM.DD2: U1.36 (DD2), U2.15 (D2)
/DRAM.DD3: U1.38 (DD3), U2.17 (D3)
/DRAM.DD4: U1.39 (DD4), U3.2 (D0)
/DRAM.DD5: U1.40 (DD5), U3.3 (D1)
/DRAM.DD6: U1.41 (DD6), U3.15 (D2)
/DRAM.DD7: U1.42 (DD7), U3.17 (D3)
/DRAM.~CAS: U1.1 (~CAS), U2.16 (~CAS), U3.16 (~CAS)
/DRAM.~RAS: U1.48 (~RAS), U2.5 (~RAS), U3.5 (~RAS)
/DRAM.~W: U1.21 (DR/W), U2.4 (~W), U3.4 (~W)
A0: J1.32, U1.7 (~RS)
D0: J1.34, U1.18 (D0), U8.11 (D0)
D1: J1.36, U1.17 (D1), U8.12 (D1)
D2: J1.38, U1.16 (D2), U8.13 (D2)
D3: J1.39, U1.15 (D3)
D4: J1.37, U1.14 (D4)
D5: J1.35, U1.13 (D5)
D6: J1.33, U1.11 (D6)
D7: J1.31, U1.10 (D7)
GND: C1.2, C2.2, C3.2, C4.2, C5.2, J1.40, J2.1, J2.2, R1.2, R6.2, U1.12 (GND), U1.23 (INIT), U1.24 (TEST), U2.1 (~G), U2.18 (GND), U3.1 (~G), U3.18 (GND), U4.1 (1OE), U4.10 (GND), U4.11 (2A3), U4.13 (2A2), U4.19 (2OE), U5.7 (GND), U5.9, U5.11, U5.13, X1.7 (GND)
unnamed: FB1.2, J2.5
unnamed: FB2.2, J2.9
unnamed: FB3.2, J2.4
unnamed: FB4.2, J2.8
unnamed: FB5.2, J2.3
unnamed: FB6.2, J2.7
unnamed: FB7.2, J2.6
unnamed: Q1.3 (B), R3.2, R4.1, U5.4
unnamed: Q1.2 (C), R5.2
unnamed: FB6.1, Q1.1 (E), R6.1
unnamed: R1.1, R2.1, U5.6
unnamed: R2.2, R3.1, U5.2
unnamed: U1.44 (B), U4.6 (1A2)
unnamed: U1.19 (CSYNC), U5.3
unnamed: U1.47 (CV), U5.1
unnamed: U1.45 (G), U4.4 (1A1)
unnamed: U1.4 (HSYNC), U4.15 (2A1)
unnamed: U1.43 (I), U4.8 (1A3), U5.5
unnamed: U1.46 (R), U4.2 (1A0)
unnamed: U1.20 (VSYNC), U4.17 (2A0)
unnamed: U1.3 (~DCLK), X1.8 (OUT)
unnamed: FB5.1, U4.18 (1Y0)
unnamed: FB3.1, U4.16 (1Y1)
unnamed: FB1.1, U4.14 (1Y2)
unnamed: FB7.1, U4.12 (1Y3)
unnamed: FB2.1, U4.3 (2Y0)
unnamed: FB4.1, U4.5 (2Y1)
unnamed: U6.2 (Q0), U8.5 (A5)
unnamed: U6.5 (Q1), U8.4 (A6)
unnamed: U6.6 (Q2), U8.3 (A7)
unnamed: U6.9 (Q3), U8.25 (A8)
unnamed: U6.12 (Q4), U8.24 (A9)
unnamed: U6.15 (Q5), U8.21 (A10)
unnamed: U6.16 (Q6), U8.23 (A11)
unnamed: U6.19 (Q7), U8.2 (A12)
R/~W: J1.6, U1.8 (R/W)
VCC: C1.1, C2.1, C3.1, C4.1, C5.1, J1.1, R4.2, R5.1, U1.37 (VCC), U2.9 (Vcc), U3.9 (Vcc), U4.20 (VCC), U5.14 (VCC), X1.14 (Vcc)
~RST: J1.2, U1.22 (~RES)
~VDC_EN: J1.29, U1.6 (~CS)
~VDC_IRQ: J1.4, U1.9 (~INT)
